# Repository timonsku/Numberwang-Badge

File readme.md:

Numberwang Badge
========

This is a stupid last minute project that came into existence for CCCamp19. If you are reading this you probably got an unpopulated PCB from me.

I did not expect that so many people got interested in it, so the documentation might be a little lacking. If you actually solder the badge and have any issue just create a Github issue here so others can profit from the discussion too.

THERE IS ONE BUG IN THE CIRCUIT. Please see the audio bodge fix png, in the hurry I misnamed a signal and it was NC when it was supposed to connect to the I2S amp. You need to solder one bodge wire, other than that all works fine.

The MCU on the board is the ATSAMD21G18, the pinout used is the same from the Adafruit Itsy Bitsy. I tried to stay as close to the Itsy Bitsy as possible so you can just refer to their documentation if you got any questions regarding pinout: https://learn.adafruit.com/introducing-itsy-bitsy-m0

Circuit wise its also really close (thanks to Adafruit for being open source), only difference is the added lipo charger which you usually find on Adafruit Feathers. It uses the same JST-PH 2.0 SMT right angle connector but the polarity is reversed to what the Adafruit batteries use! Why? Because I can't buy them in Germany and all other batteries with this connector use the opposite polarity so I went with what the batteries on Amazon offer.

Quick note on the BOM, the design isn't all that smart, there are some components that appear in both 0603 and 0805, you can get away with using just 0603 or just 0805, no need to get both sizes.

I think you can get all components from Mouser if you want, they will just be more expensive than getting them from LCSC. Especially the JST-PH, if you need that from 'not LCSC' go with Digikey or buy the over priced reselled one that is available from Mouser as an Adafruit product.

If anything is unclear in the BOM, please create an issue, I respond fairly quickly usually.

There is an SWD testpad pinout in 2.54mm raster, I used pogo pins for programming but you can also just use a right angle pin header that you press against the pad. Might be a bit flaky but works for flashing the bootloader. Here a tutorial from Adafruit that explains flashing with different programmers (can also use a Pi or other ARM MCU to flash if you dont got an SWD capable flasher)
https://learn.adafruit.com/how-to-program-samd-bootloaders

UF2 bootloader binary is provided in the repo as well as a slightly customized CircuitPython firmware (same as Itsy Bitsy M0 just different flash IC set). When using online docs you can always refer to Itsy Bitsy M0.
Same for Arduino, just get the Adafruit SAMD board package and choose Itsy Bitsy M0 as target.

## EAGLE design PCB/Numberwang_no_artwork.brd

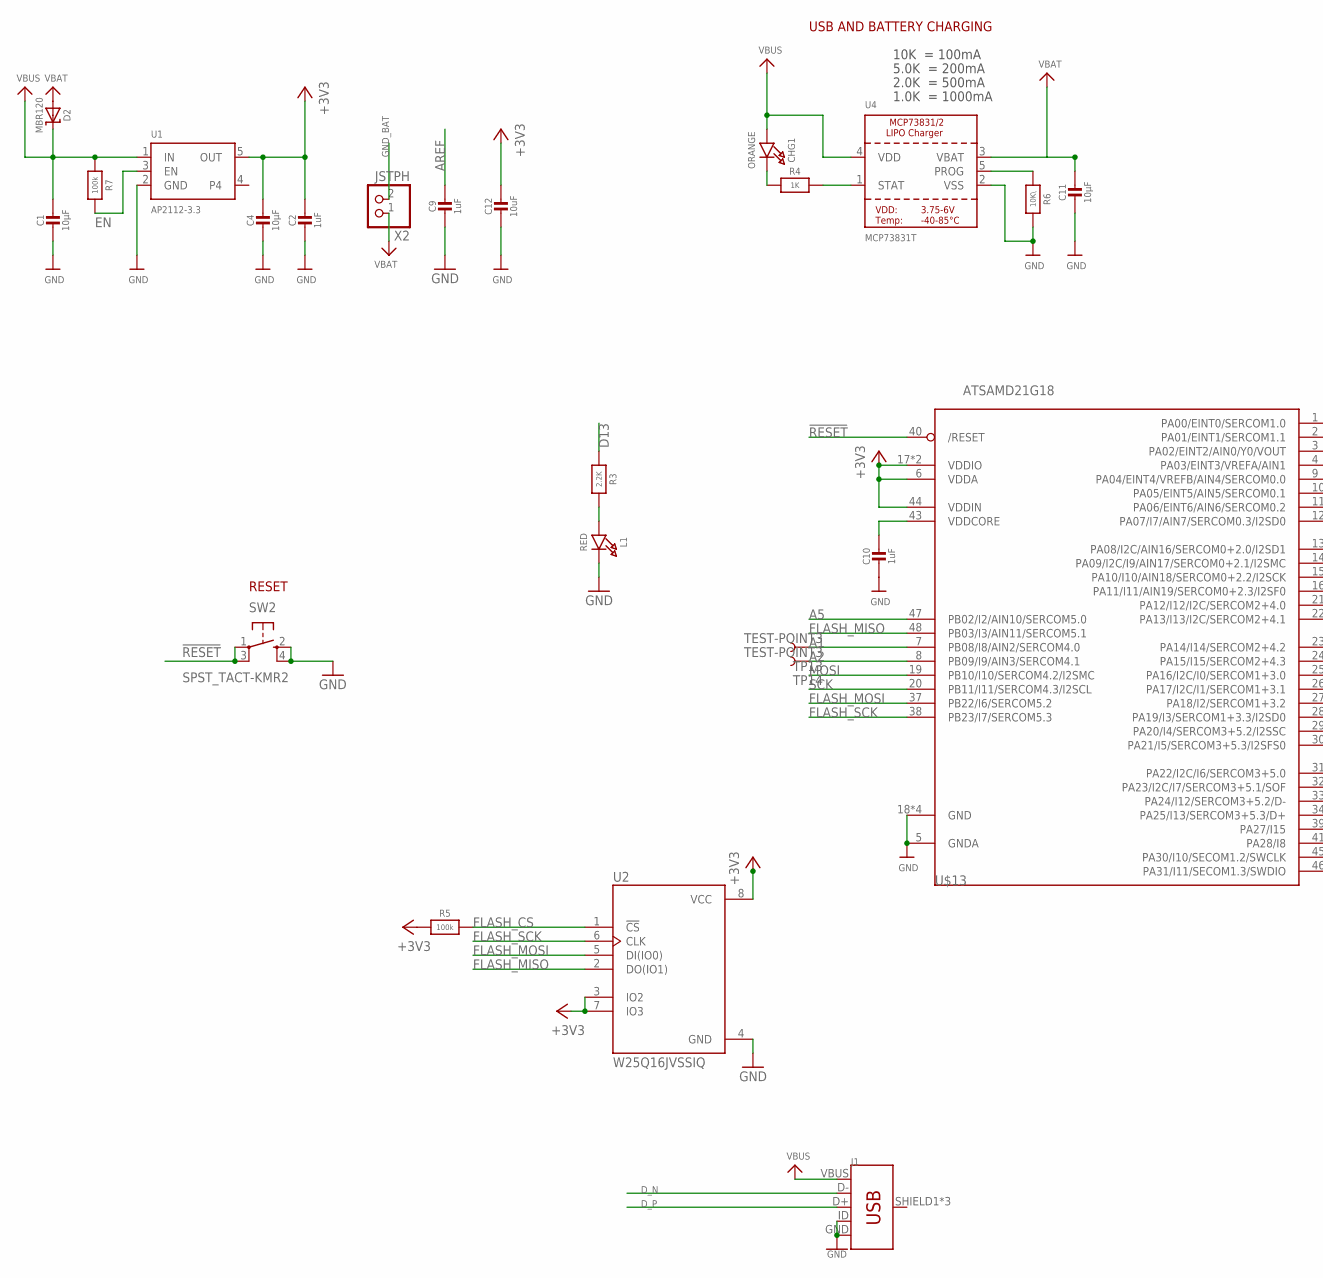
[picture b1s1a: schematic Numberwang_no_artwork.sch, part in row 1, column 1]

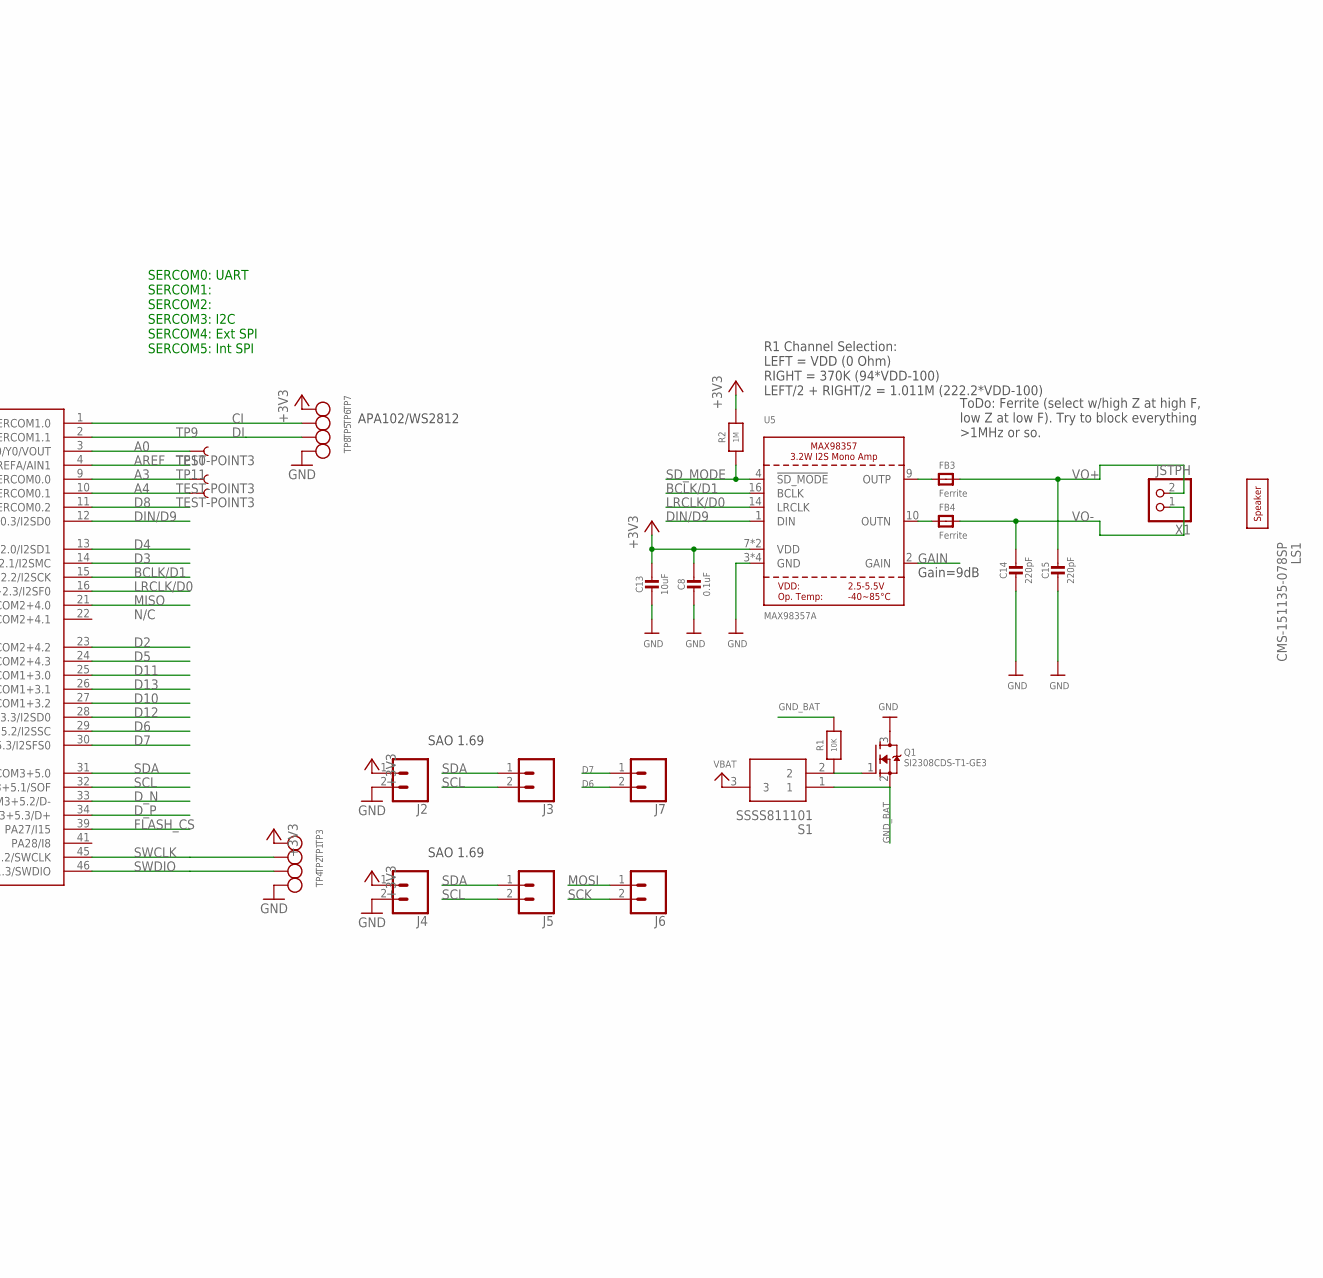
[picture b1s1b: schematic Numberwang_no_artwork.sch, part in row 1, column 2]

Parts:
C1, C4, C11: 10µF; _0805MP
C2, C9, C10: 1uF; _0603MP
C8: 0.1uF; _0805MP
C12, C13: 10uF; _0805MP
C14, C15: 220pF; _0805MP
CHG1: ORANGE; CHIPLED_0805_NOOUTLINE
D2: MBR120; SOD-123
FB3, FB4: Ferrite; 0603
J1: USB_MICRO-B_FEMALE-SMT; USB-B-MICRO-SMD
J2, J3, J4, J5, J6, J7: CONN_02; 1X02
L1: RED; CHIPLED_0805_NOOUTLINE
LS1: CMS-151135-078SP; CMS151135078SP
Q1: SI2308CDS-T1-GE3; SOT23-WIDE
R1: 10K; _0805MP
R2: 1M; _0805MP
R3: 2.2K; _0603MP
R4: 1K; _0603MP
R5, R7: 100k; _0603MP
R6: 10K\; _0603MP
S1: SSSS811101
SW2: SPST_TACT-KMR2; KMR2
TP1, TP2, TP3, TP4, TP5, TP6, TP7, TP8: TESTPOINTROUND2MM; TESTPOINT_ROUND_2MM
TP9, TP10, TP11, TP13, TP14: TEST-POINT3; PAD.03X.03
U1: AP2112-3.3; SOT23-5
U2: W25Q16JVSSIQ; SOIC127P790X216-8N
U4: MCP73831T; SOT23-5@1
U5: MAX98357A; QFN16_3MM
U$13: ATSAMD21G18; TQFN48_7MM
X1, X2: JSTPH; JSTPH2

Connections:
!RESET: SW2.1, SW2.3 (P1), U$13.40 (/RESET)
+3V3: C2.1, C4.1, C8.1, C12.1, C13.1, J2.1, J4.1, R2.2, R5.1, TP3.P$1, TP7.P$1, U1.5 (OUT), U2.3 (IO2), U2.7 (IO3), U2.8 (VCC), U5.7 (VDD), U5.8 (VDD), U$13.6 (VDDA), U$13.17 (VDDIO), U$13.36 (VDDIO), U$13.44 (VDDIN)
A0: TP9.P$1, U$13.3 (PA02/EINT2/AIN0/Y0/VOUT)
A1: TP13.P$1, U$13.7 (PB08/I8/AIN2/SERCOM4.0)
A2: TP14.P$1, U$13.8 (PB09/I9/AIN3/SERCOM4.1)
A3: TP10.P$1, U$13.9 (PA04/EINT4/VREFB/AIN4/SERCOM0.0)
A4: TP11.P$1, U$13.10 (PA05/EINT5/AIN5/SERCOM0.1)
A5: U$13.47 (PB02/I2/AIN10/SERCOM5.0)
AREF: C9.1, U$13.4 (PA03/EINT3/VREFA/AIN1)
BCLK/D1: U5.16 (BCLK), U$13.15 (PA10/I10/AIN18/SERCOM0+2.2/I2SCK)
CI: TP6.P$1, U$13.1 (PA00/EINT0/SERCOM1.0)
D2: U$13.23 (PA14/I14/SERCOM2+4.2)
D3: U$13.14 (PA09/I2C/I9/AIN17/SERCOM0+2.1/I2SMC)
D4: U$13.13 (PA08/I2C/AIN16/SERCOM0+2.0/I2SD1)
D5: U$13.24 (PA15/I15/SERCOM2+4.3)
D6: J7.2, U$13.29 (PA20/I4/SERCOM3+5.2/I2SSC)
D7: J7.1, U$13.30 (PA21/I5/SERCOM3+5.3/I2SFS0)
D8: U$13.11 (PA06/EINT6/AIN6/SERCOM0.2)
D10: U$13.27 (PA18/I2/SERCOM1+3.2)
D11: U$13.25 (PA16/I2C/I0/SERCOM1+3.0)
D12: U$13.28 (PA19/I3/SERCOM1+3.3/I2SD0)
D13: R3.1, U$13.26 (PA17/I2C/I1/SERCOM1+3.1)
DI: TP5.P$1, U$13.2 (PA01/EINT1/SERCOM1.1)
DIN/D9: U5.1 (DIN), U$13.12 (PA07/I7/AIN7/SERCOM0.3/I2SD0)
D_N: J1.D-, U$13.33 (PA24/I12/SERCOM3+5.2/D-)
D_P: J1.D+, U$13.34 (PA25/I13/SERCOM3+5.3/D+)
EN: R7.2, U1.3 (EN)
FLASH_CS: R5.2, U2.1 (!CS), U$13.39 (PA27/I15)
FLASH_MISO: U2.2 (DO(IO1)), U$13.48 (PB03/I3/AIN11/SERCOM5.1)
FLASH_MOSI: U2.5 (DI(IO0)), U$13.37 (PB22/I6/SERCOM5.2)
FLASH_SCK: U2.6 (CLK), U$13.38 (PB23/I7/SERCOM5.3)
GAIN: U5.2 (GAIN)
GND: C1.2, C2.2, C4.2, C8.2, C9.2, C10.2, C11.2, C12.2, C13.2, C14.2, C15.2, J1.GND, J1.ID, J2.2, J4.2, L1.C, Q1.3 (D), R6.2, SW2.2 (S), SW2.4 (S1), TP4.P$1, TP8.P$1, U1.2 (GND), U2.4 (GND), U4.2 (VSS), U5.3 (GND), U5.11 (GND), U5.15 (GND), U5.THERMAL (GND), U$13.5 (GNDA), U$13.18 (GND), U$13.35 (GND), U$13.42 (GND), U$13.THERMAL (GND)
GND_BAT: Q1.2 (S), R1.2, S1.1, X2.2
LRCLK/D0: U5.14 (LRCLK), U$13.16 (PA11/I11/AIN19/SERCOM0+2.3/I2SF0)
MISO: U$13.21 (PA12/I12/I2C/SERCOM2+4.0)
MOSI: J6.1, U$13.19 (PB10/I10/SERCOM4.2/I2SMC)
unnamed: FB4.1, U5.10 (OUTN)
unnamed: L1.A, R3.2
unnamed: FB3.1, U5.9 (OUTP)
unnamed: Q1.1 (G), R1.1, S1.2
unnamed: CHG1.C, R4.1
unnamed: R4.2, U4.1 (STAT)
unnamed: R6.1, U4.5 (PROG)
SCK: J6.2, U$13.20 (PB11/I11/SERCOM4.3/I2SCL)
SCL: J3.2, J5.2, U$13.32 (PA23/I2C/I7/SERCOM3+5.1/SOF)
SDA: J3.1, J5.1, U$13.31 (PA22/I2C/I6/SERCOM3+5.0)
SD_MODE: R2.1, U5.4 (!SD_MODE)
SWCLK: TP1.P$1, U$13.45 (PA30/I10/SECOM1.2/SWCLK)
SWDIO: TP2.P$1, U$13.46 (PA31/I11/SECOM1.3/SWDIO)
VBAT: C11.1, D2.A, S1.3, U4.3 (VBAT), X2.1
VBUS: C1.1, CHG1.A, D2.C, J1.VBUS, R7.1, U1.1 (IN), U4.4 (VDD)
VDDCORE1: C10.1, U$13.43 (VDDCORE)
VO+: C15.1, FB3.2, X1.2
VO-: C14.1, FB4.2, X1.1

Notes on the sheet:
RESET
N/C
SERCOM0: UART SERCOM1: SERCOM2: SERCOM3: I2C SERCOM4: Ext SPI SERCOM5: Int SPI
10K = 100mA
5.0K = 200mA
2.0K = 500mA
1.0K = 1000mA
USB AND BATTERY CHARGING
APA102/WS2812
SAO 1.69
R1 Channel Selection: LEFT = VDD (0 Ohm) RIGHT = 370K (94*VDD-100) LEFT/2 + RIGHT/2 = 1.011M (222.2*VDD-100)
ToDo: Ferrite (select w/high Z at high F, low Z at low F). Try to block everything >1MHz or so.
Gain=9dB

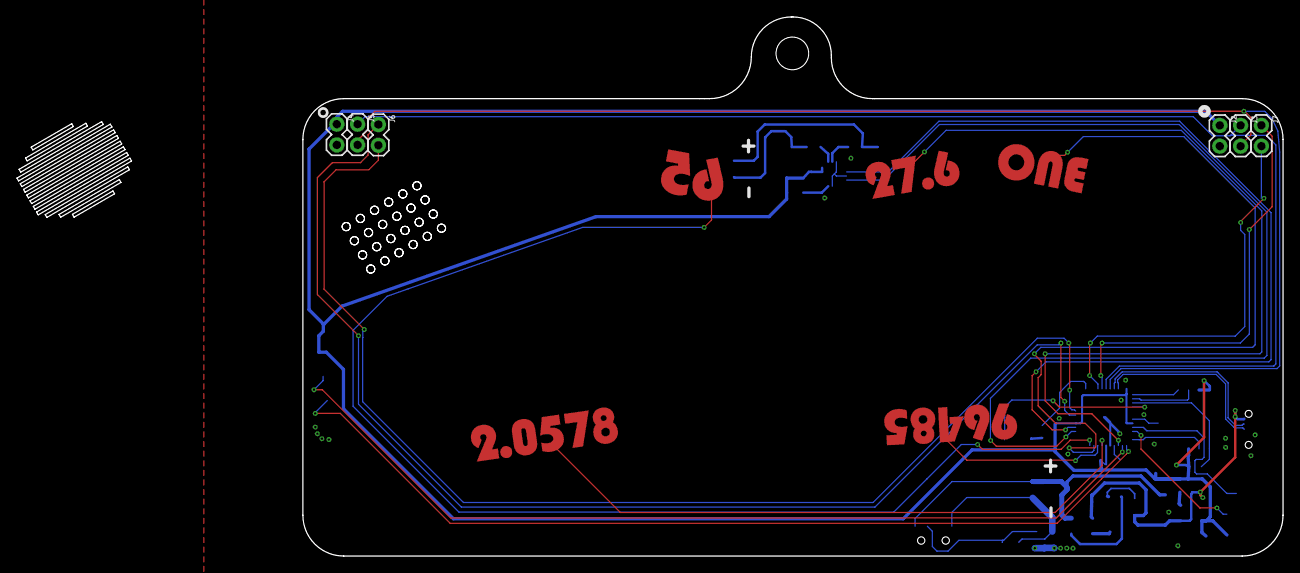
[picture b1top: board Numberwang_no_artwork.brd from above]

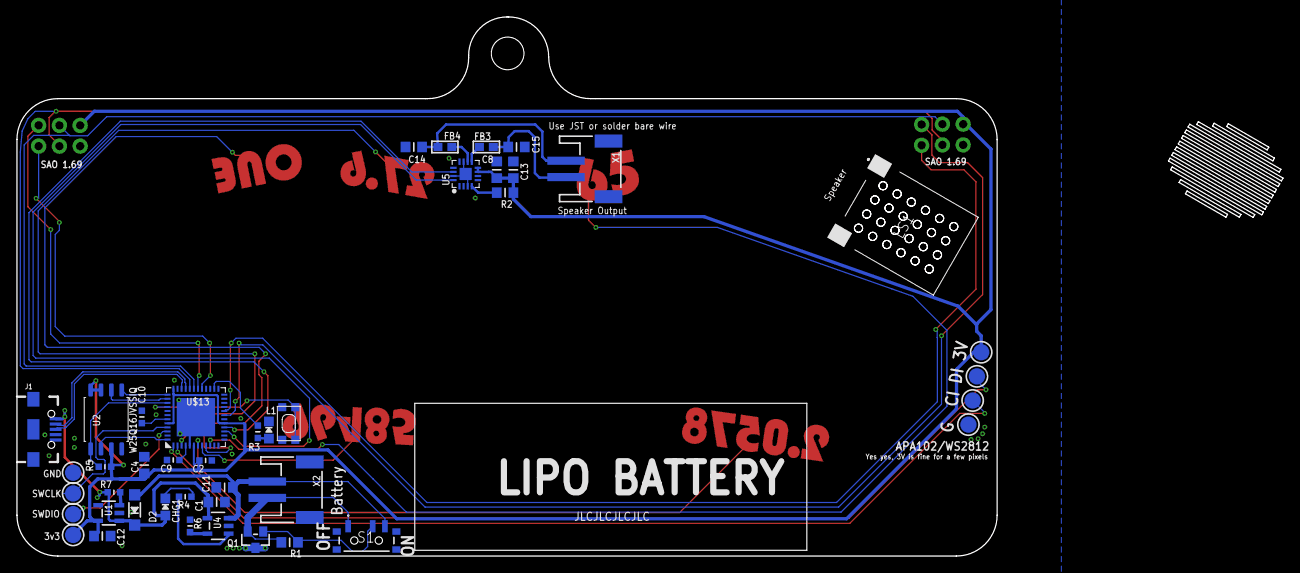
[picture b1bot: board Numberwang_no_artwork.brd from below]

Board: 2 copper layers, 155.0 x 66.0 mm, 54 parts (43 on the bottom side), 44 nets.

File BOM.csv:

Qty;Value;Device;Package;Parts;Description;Order Link;DESCRIPTION;MANUFACTURER_NAME;MANUFACTURER_PART_NUMBER;MF;MOUSER_PART_NUMBER;MOUSER_PRICE-STOCK;MP;PACKAGE;PRICE;PROD_ID;RS_PART_NUMBER;RS_PRICE-STOCK
1;;USB_MICRO-B_FEMALE-SMT;USB-B-MICRO-SMD;J1;USB Type Micro-B Connector;https://lcsc.com/product-detail/Micro-USB-Connectors_Korean-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;This part on mouser should work just as fine https://www.mouser.de/ProductDetail/Hirose-Connector/ZX62-B-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;;;;;;;;;CONN-11752;;
1;0.1uF;CAP_CERAMIC_0805MP;_0805MP;C8;Ceramic Capacitors;Generic;;Generic;;;;;;;;;;
2;100k;RESISTOR_0603MP;_0603MP;R5, R7;Resistors;Generic;;Generic;;;;;;;;;;
1;10K;RESISTOR_0805MP;_0805MP;R1;Resistors;Generic;;Generic;;;;;;;;;;
1;10K;RESISTOR_0603MP;_0603MP;R6;Resistors;Generic;;Generic;;;;;;;;;;
2;10uF;CAP_CERAMIC_0805MP;_0805MP;C12, C13;Ceramic Capacitors;Generic;;Generic;;;;;;;;;;
3;10µF;CAP_CERAMIC_0805MP;_0805MP;C1, C4, C11;Ceramic Capacitors;Generic;;Generic;;;;;;;;;;
1;1K;RESISTOR_0603MP;_0603MP;R4;Resistors;Generic;;Generic;;;;;;;;;;
1;1M;RESISTOR_0805MP;_0805MP;R2;Resistors;Generic;;Generic;;;;;;;;;;
3;1uF;CAP_CERAMIC_0603MP;_0603MP;C2, C9, C10;Ceramic Capacitors;Generic;;Generic;;;;;;;;;;
1;2.2K;RESISTOR_0603MP;_0603MP;R3;Resistors;Generic;;Generic;;;;;;;;;;
2;220pF;CAP_CERAMIC_0805MP;_0805MP;C14, C15;Ceramic Capacitors;Generic;;Generic;;;;;;;;;;
1;AP2112-3.3;VREG_SOT23-5;SOT23-5;U1;SOT23-5 Fixed Voltage Regulators;https://lcsc.com/product-detail/Low-Dropout-Regulators-LDO_D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;;;AP2112K-3-3;;;;;;;;;
1;ATSAMD21G18;ATSAMD21G_QFN;TQFN48_7MM;U$13;;https://www.mouser.de/ProductDetail/Microchip-Technology-Atm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;;Microchip;ATSAMD21G18A-MUT;;;;;;;;;
1;CMS-151135-078SP;CMS-151135-078SP;CMS151135078SP;LS1;Speakers & Transducers 0.7W 8ohm 550Hz 15x11mm Solder Pads;https://www.mouser.com/Search/Refine.aspx?Keyword=490-CMS-15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;Speakers & Transducers 0.7W 8ohm 550Hz 15x11mm Solder Pads;CUI;CMS-151135-078L100;;490-CMS-151135-078L100;https://www.mouser.com/Search/Refine.aspx?Keyword=490-CMS-15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;;;;;;
2;Ferrite;FERRITE;603;FB3, FB4;Ferrite Bead;https://www.mouser.de/ProductDetail/CUI/CMS-151135-078L100?q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;;;MAF1608GAD471CT000;;;;;;;;;
2;JSTPH;CON_JST_PH_2PIN;JSTPH2;X1, X2;JST 2-Pin Right-Angle Connector;https://lcsc.com/product-detail/Wire-To-Board-Wire-To-Wire-C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;;;;;;;;;;;;
1;MAX98357A;AUDIOAMP_MAX98357;QFN16_3MM;U5;MAX98357 - 3.2W I2S Mono Audio Amp;https://www.mouser.de/ProductDetail/Maxim-Integrated/MAX9835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;;;;;;;;;;;;
1;MBR120;DIODE-SCHOTTKYSOD-123;SOD-123;D2;2A rating or better, SOD-214 package also works (I used that because I still had it) f.e. B230A;https://lcsc.com/product-detail/Schottky-Barrier-Diodes-SBD_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;;;;;;;;;;;;
1;MCP73831T;MCP73831/2;SOT23-5@1;U4;MCP73831/2 LIPO Charger SOT23-5;https://www.mouser.de/ProductDetail/Microchip-Technology/MCP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;;;;;;;;;;;;
1;ORANGE;LED0805_NOOUTLINE;CHIPLED_0805_NOOUTLINE;CHG1;LED;Generic;;;;;;;;;;;;
1;RED;LED0805_NOOUTLINE;CHIPLED_0805_NOOUTLINE;L1;LED;Generic;;;;;;;;;;;;
1;SI2308CDS-T1-GE3;MOSFET-NWIDE;SOT23-WIDE;Q1;N-Channel Mosfet;https://www.mouser.de/ProductDetail/78-SI2308CDS-T1-GE3;;;SI2308CDS-T1-GE3;;;;;;;;;
1;SPST_TACT-KMR2;SPST_TACT-KMR2;KMR2;SW2;SMT 6mm switch, EVQQ2 series;https://lcsc.com/product-detail/Tactile-Switches_C-K_KMR221G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;;;;;;;;;;;;
1;SSSS811101;SSSS811101;SSSS811101;S1;Slide Switches SPDT HORZ GRND 1.5mm;https://lcsc.com/product-detail/Toggle-Switches_ALPS_SSSS811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;Slide Switches SPDT HORZ GRND 1.5mm;ALPS;SSSS811101;;688-SSSS811101;https://www.mouser.com/Search/Refine.aspx?Keyword=688-SSSS811101;;;;;1238939;http://uk.rs-online.com/web/p/products/1238939
1;W25Q16JVSSIQ;W25Q16JVSSIQ;SOIC127P790X216-8N;U2;3v 16m-Bit Serial Flash Memory With Dual;https://lcsc.com/product-detail/FLASH_Winbond-Elec-W25Q16JVS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; 3v 16m-Bit Serial Flash Memory With Dual ;;;Winbond Electronics;;;W25Q16JVSSIQ;SOIC-8 Winbond;None;;;

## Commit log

2019-08-27 Added BOM and PCB source files

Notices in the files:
parts and their libraries:
microbuilder: This work is placed in the public domain, and may be freely used for commercial and non-commercial work with the following conditions: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
SparkFun-Connectors: Licensing: Creative Commons ShareAlike 4.0 International - https://creativecommons.org/licenses/by-sa/4.0
